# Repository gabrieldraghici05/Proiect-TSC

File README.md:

# Proiect-TSC

## Descriere generală

InkTime este un smartwatch construit în jurul microcontroller-ului nRF52840, utilizând un afișaj E-Paper. Proiectul este dezvoltat în Autodesk Fusion: de la concepția schemelor și rutarea unui PCB pe 4 straturi, până la integrarea mecanică finală în carcasă.

Principalele caracteristici:
- Procesare: nRF52840 (Cortex-M4F) cu conectivitate Bluetooth 5.0 integrată
- Afișaj: Ecran E-Paper (SPI)
- Senzori: Accelerometru BMA423 pentru pedometru și gesturi
- Baterie LiPo cu circuit de încărcare dedicat (BQ25180).
- Regulator DC/DC (RT6160) pentru o tensiune stabilă de 3.3V
- Fuel Gauge (MAX17048) pentru monitorizarea nivelului bateriei
- Driver haptic (DRV2605) pentru feedback
- Conectivitate USB-C pentru încărcare
- 3 butoane fizice pentru interacțiune

---

## Diagrama bloc

```text
                         +-------------------+
                         |    Baterie LiPo   |
                         +--------+----------+
                                  |
                         +--------v----------+
                         |  LiPo Charger     |  <-- USB-C (5V / VBUS)
                         |  BQ25180YBGR      |
                         +--------+----------+
                                  | VBAT (3.7-4.2V)
                         +--------v----------+
                         |  Fuel Gauge       |  <-- I2C --> nRF52840
                         |  MAX17048G+T10    |
                         +--------+----------+
                                  |
                         +--------v----------+
                         |  DC/DC Regulator  |  <-- I2C --> nRF52840
                         |  RT6160AWSC       |
                         +--------+----------+
                                  | 3V3
          +-----------------------+-----------------------+
          |                       |                       |
+---------v---------+   +---------v---------+   +---------v---------+
|   nRF52840 (U1)   |   |  ESD Protection   |   |   Butoane (x3)    |
|   Microcontroller |   |  USBLC6-2SC6Y     |   |   EVP-AKE31A      |
+---------+---------+   +-------------------+   +-------------------+
          |
    +-----+------+------+------+
    |            |      |      |
+---v---+  +----v--+  +-v---+ +-v---------+
| SPI   |  |  I2C  |  | SWD | | GPIO/ANT  |
+---+---+  +---+---+  +-----+ +-----------+
    |          |
+---v---+   +--+--+--+--+
|E-Paper|   | IMU | Haptic|
|Display|   |BMA423|DRV2605|
+-------+   +-------+-----+
```

---
## Bill of Materials (BOM)

| Cantitate | Componenta | Descriere | Referinta | 
|:---------:|:----------:|:---------:|:---------:|
| 1 | nRF52840 | Microcontroller ARM Cortex-M4, BT 5.0 | U1 | 
| 1 | BQ25180YBGR | LiPo Charger IC, 8-DSBGA | IC1 | 
| 1 | DRV2605YZFR | Haptic Driver ERM/LRA, 9-BGA | IC2 |
| 1 | BMA423 | IMU Accelerometru triaxial 12-bit | IC3 |
| 1 | MAX17048G+T10 | Fuel Gauge 1-Cell ModelGauge | U3 | 
| 1 | RT6160AWSC | Buck-Boost DC/DC Regulator I2C, 15-WL-CSP | IC9 | 
| 1 | USBLC6-2SC6Y | ESD Protection TVS Diode, SOT-23-6 | D3 | 
| 1 | KH-TYPE-C-16P | Conector USB-C 16 pini | J4 |
| 1 | 503480-2400 | Conector FPC/FFC 0.5mm 24 circuite | J1 | 
| 1 | DMG2305UX-7 | P-Channel MOSFET 20V/4.2A SOT-23 | Q2 | 
| 1 | SI1308EDL-T1-GE3 | N-Channel MOSFET 30V/1.5A SC-70 | Q3 | 
| 3 | MBR0530 | Dioda Schottky 30V/500mA SOD-123 | D1, D2, D5 | 
| 3 | EVP-AKE31A | Buton tactil SMD ultra-subtire | SW_DN, SW_ENT, SW_UP | 
| 1 | 2450AT18B100E | Antena 2.45GHz SMD | ANT1 | 
| 1 | FTC252012SR47MBCA | Inductor SMD 0.47uH 2016 | L7 | 
| 1 | 744043680 | Inductor SMD 68uH WE-TPC | L5 |
| 1 | TC2030-IDC | Conector Tag-Connect 6 pini SWD | J2 |
| 1 | X1 (32MHz) | Crystal 32MHz 2016 SMD | X1 |
| 1 | X2 (32.768kHz) | Crystal 32.768kHz 3215 SMD | X2 | 
| ~50 | Condensatoare SMD | 0201/0402, diverse valori (1pF - 22uF) | Cx | 
| ~15 | Rezistoare SMD | 0201, diverse valori (2.2Ω - 10kΩ) | Rx |
| ~4 | Inductoare SMD | 0402, diverse valori (3.9nH - 15nH, 10uH) | Lx |
| 14 | Test Pad TP20R | Test pad-uri SMD 2mm | TP_* |
| 1 | Solder Jumper SJ | Jumper SMD | SJ1 |

---

## Funcționalitate hardware

#### Componente și roluri
Sistemul este coordonat de nRF52840, care gestionează atât logica internă, stările de sleep pentru economisirea energiei, cât și comunicarea Bluetooth.

* Alimentare și Power Management: Bateria Li-Po este conectată direct la test pad-urile plăcii pentru a economisi spațiu pe verticală. Încărcarea este gestionată de BQ25180. Tensiunea bateriei este monitorizată precis de Fuel Gauge-ul MAX17048, iar alimentarea componentelor logice la 3.3V este asigurată de convertorul DC/DC RT6160 (ales în detrimentul unui LDO pentru un randament energetic superior).

* Interfața cu utilizatorul: Afișajul E-Paper este controlat prin SPI pentru o viteză mare de transfer, consumând energie doar la actualizarea imaginii. Input-ul se face prin 3 butoane tactile cu debouncing software, iar feedback-ul este asigurat de driverul haptic DRV2605 conectat la un actuator de tip shaker.

* Senzori: Accelerometrul BMA423 este legat pe magistrala I2C și este folosit pentru funcții precum ridicarea mâinii pentru aprindere (wake-on-wrist).

#### Interfețe de comunicație
* I2C: LiPo Charger, DC/DC, IMU, Fuel Gauge, Haptic Driver. (Folosește rezistențe de pull-up externe pentru stabilitate).

* SPI: E-Paper Display Connector (viteză mare de transmisie a datelor grafice).

---

## Pinii nRF52840

| Pin nRF52840 | Semnal | Modul conectat | Interfata | Descriere |
| :--------- | :--------- | :--------- | :--------- | :--------- |
| P0.02/AIN0 | SCK | E-Paper Display | SPI | Clock serial SPI |
| P0.03/AIN1 | MOSI | E-Paper Display | SPI | Date catre display (Master Out Slave In) |
| P0.05/AIN3 | CS | E-Paper Display | SPI | Chip Select display |
| P0.15 | EPD_RST | E-Paper Display | GPIO | Reset display |
| P0.16 | EPD_DC | E-Paper Display | GPIO | Data/Command select |
| P0.17 | EPD_BUSY | E-Paper Display | GPIO | Stare ocupata display |
| P0.06 | SCL | IMU, LiPo Charger, DC/DC, Fuel Gauge, Haptic | I2C | Clock linie I2C |
| P0.07 | SDA | IMU, LiPo Charger, DC/DC, Fuel Gauge, Haptic | I2C | Date linie I2C |
| P0.08 | IMU_INT2 | BMA423 | GPIO | Intrerupere 2 accelerometru |
| P1.08 | IMU_INT1 | BMA423 | GPIO | Intrerupere 1 accelerometru |
| P0.10/NFC2 | FUELGAUGE_ALT | MAX17048 | GPIO | Alarma nivel scazut baterie |
| P0.11 | CHARGER_PG | BQ25180 | GPIO | Semnal Power Good charger |
| P0.12 | HAPTIC_EN | DRV2605 | GPIO | Enable driver haptic |
| P0.13 | BTN_UP | SW_UP | GPIO | Buton sus |
| P0.14 | BTN_ENT | SW_ENT | GPIO | Buton enter/confirmare |
| P1.02 | BTN_DN | SW_DN | GPIO | Buton jos |
| D+ / D- | USB_DP / DM | USB-C / ESD | USB | Date USB diferentiale |
| VBUS | 5V USB | LiPo Charger | - | Alimentare 5V din USB |
| SWDIO / CLK | SWDIO / CLK| TC2030-IDC (J2) | SWD | Date programare/debug |
| SWO | SWO | TC2030-IDC (J2) | SWD | Trace output |
| P0.18/RESET | RESET | TC2030-IDC (J2) | GPIO | Reset hardware microcontroller |
| ANT | RF | 2450AT18B100E | RF | Antena Bluetooth 2.4GHz |
| XC1, XC2 | XTAL_32M | X1 (32 MHz) | Clock | Sursa de ceas principala |
| XL1, XL2 | XTAL_32K | X2 (32.768 kHz) | Clock | Sursa de ceas RTC (low power) |

---
## Design PCB si Modelare Mecanică 3D

### Stackup PCB — 4 straturi
Placa a fost realizată pe 4 straturi pentru a asigura o integritate a semnalului excelentă și o rutare compactă:

* Top (L1): Rutare semnal + componente SMD.

* L2: Plan de masă (GND solid) care oferă un return path scurt pentru toate semnalele.

* L3: Rutare secundară — acest strat a fost utilizat în principal pentru rezolvarea manuală a Airwire-urilor rămase în urma procesului de autorutare, asigurând finalizarea tuturor conexiunilor complexe.

* Bottom (L4): Rutare semnal secundar.

### Decizii de design notabile
* Decupaj Antenă (RF): Antena ceramică este poziționată pe marginea plăcii. Sub aceasta s-a realizat un decupaj complet al substratului pe toate planurile (ground clearance) pentru performanță radio optimă.

* Via-in-Pad: Pentru componentele BGA dense, a fost utilizată tehnologia via-in-pad pentru a salva spațiu, rutând semnalele direct din pad-uri.

* Pad-uri de Test: Au fost adăugate 14 test pad-uri pentru semnalele vitale (3V3, VBAT, SWD, I2C), pentru lipirea directă a bateriei.

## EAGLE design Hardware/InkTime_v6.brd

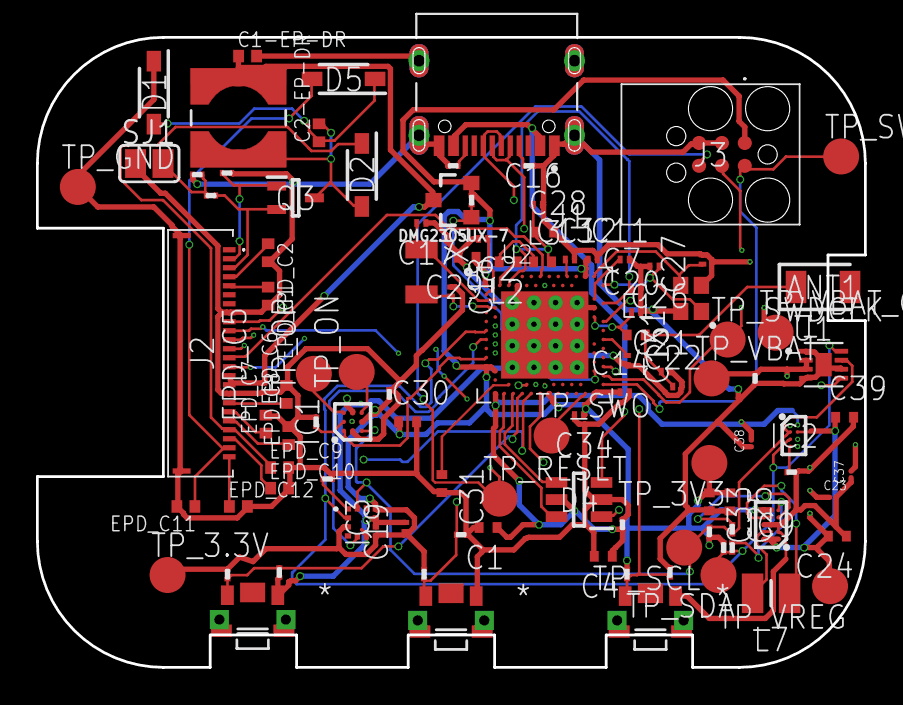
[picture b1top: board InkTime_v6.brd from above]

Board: 4 copper layers, 46.0 x 35.0 mm, 105 parts (0 on the bottom side), 70 nets.

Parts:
ANT1: 2450AT18B100E; 2450AT18B100E_ANTC3216X140N
C1, C29, C30, C31: 4.7μF; NORDIC_NRF_3_RESC0402_L
C1-EP-DR: 10uF; PERFECT_0402_0402
C2, C12, C14, C19, C34: 100nF; NORDIC_NRF_3_RESC0201_L
C2-EP-DR: 4.7uF/25V; PERFECT_0402_0402
C3, C5, C10, C32: 1uF; GRM011R60J152KE01L_1_0201
C4: 4.7uF; NORDIC_NRF_3_RESC0402_L
C6, C8, C9: 0.1uF; GRM011R60J152KE01L_1_0201
C7, C13, C22: N.C.; NORDIC_NRF_3_RESC0201_L
C11: 100pF; NORDIC_NRF_3_RESC0201_L
C15: 820pF; NORDIC_NRF_3_RESC0201_L
C16: 47nF; NORDIC_NRF_3_RESC0201_L
C17, C18, C26, C27: 12pF; NORDIC_NRF_3_RESC0201_L
C20, C21: 1pF; NORDIC_NRF_3_RESC0201_L
C23: 0.1uF; GRM011R60J152KE01L_2_CAPC0201X13N
C24, C39: 10uF; NORDIC_NRF_3_RESC0402_L
C25, C33: 22uF; NORDIC_NRF_3_RESC0402_L
C28: 1.0μF; NORDIC_NRF_3_RESC0402_L
C37, C38: 1uF; GRM011R60J152KE01L_2_CAPC0201X13N
D1, D2, D5: MBR0530; ESP32_C6_LIBRARY_5_SOD3716X135N
D4: USBLC6-2SC6Y; ESP32_C6_LIBRARY_3_SOT95P280X145-6N
DMG2305UX-7: 20V/4.2A/52mΩ/1.4W; ESP32_C6_LIBRARY_4_ESP32_C6_LIBRARY_4_ESP32_C6_LIBRARY_4_ES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
EPD_C1, EPD_C2, EPD_C6, EPD_C7, EPD_C8, EPD_C9, EPD_C10, EPD_C11, EPD_C12: 1uF/50V; PERFECT_0402_0402
EPD_C5: 0.1uF/50V; NORDIC_NRF_3_RESC0201_L
IC1: DRV2605YZFR; DRV2605YZFR_BGA9C50P3X3_144X144X62
IC2: BQ25180YBGR; BQ25180YBGR_BGA8C40P2X4_100X155X50
IC3: BMA421; BMA423_BMA423
IC9: RT6160AWSC; RT6160AWSC_BGA15C40P3X5_140X230X60
J1: KH-TYPE-C-16P; KH-TYPE-C-16P_KINGHELM_KH-TYPE-C-16P
J2: 503480-2400; 503480-2400_5034802400
J3: TC2030-IDC; TC2030-IDC_TC2030IDC
L1: 3.9nH; NORDIC_NRF_2_RESC0402_L
L2: 10μH; NORDIC_NRF_2_RESC0402_L
L3: 15nH; NORDIC_NRF_2_RESC0402_L
L5: 68uH; ESP32_C6_LIBRARY_2_IND_4828-WE-TPC_WRE
L7: FTC252012SR47MBCA; MLP2016SR47MT0S1_INDC2016X100N
Q3: SI1308EDL-T1-GE3; ESP32_C6_LIBRARY_6_SOT65P210X110-3N
R1, R2_EP_DR, R5, R7, R8: 10K; CPF0201D7K68C1_0201
R1_EP_DR1: 0.47; CPF0201D7K68C1_0201
R1_USB, R2_USB: 5K1; CPF0201D7K68C1_0201
R2, R3, R4: 0; CPF0201D7K68C1_0201
R17, R18: 3K3; ERA-1AEB3401C_0201
R_PWR_EPD: 10K; CPF0201D7K68C1_0201
R_TYPE_SEL: 2.2; CPF0201D7K68C1_0201
SJ1: ESP32_C6_LIBRARY_7_JUMPER_SJ
SW_DN: 2025-10-22_07-23-44_LIBRARY_EVP-AKE31ASW_EVP-AKE3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; 2025-10-22_07-23-44_LIBRARY_SW_EVP-AKE31A_PAN
SW_ENT: 2025-10-22_07-23-44_LIBRARY_EVP-AKE31ASW_EVP-AKE3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; 2025-10-22_07-23-44_LIBRARY_SW_EVP-AKE31A_PAN
SW_UP: 2025-10-22_07-23-44_LIBRARY_EVP-AKE31ASW_EVP-AKE3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; 2025-10-22_07-23-44_LIBRARY_SW_EVP-AKE31A_PAN
TP_3.3V, TP_3V3: HECTOR_WATCH_1_TPTP20R; HECTOR_WATCH_1_TP20R
TP_GND: HECTOR_WATCH_1_TPTP20R; HECTOR_WATCH_1_TP20R
TP_ON: HECTOR_WATCH_1_TPTP20R; HECTOR_WATCH_1_TP20R
TP_OP: HECTOR_WATCH_1_TPTP20R; HECTOR_WATCH_1_TP20R
TP_RESET: HECTOR_WATCH_1_TPTP20R; HECTOR_WATCH_1_TP20R
TP_SCL: HECTOR_WATCH_1_TPTP20R; HECTOR_WATCH_1_TP20R
TP_SDA: HECTOR_WATCH_1_TPTP20R; HECTOR_WATCH_1_TP20R
TP_SWDCLK: HECTOR_WATCH_1_TPTP20R; HECTOR_WATCH_1_TP20R
TP_SWIO: HECTOR_WATCH_1_TPTP20R; HECTOR_WATCH_1_TP20R
TP_SWO: HECTOR_WATCH_1_TPTP20R; HECTOR_WATCH_1_TP20R
TP_VBAT: HECTOR_WATCH_1_TPTP20R; HECTOR_WATCH_1_TP20R
TP_VBAT_GND: HECTOR_WATCH_1_TPTP20R; HECTOR_WATCH_1_TP20R
TP_VREG: HECTOR_WATCH_1_TPTP20R; HECTOR_WATCH_1_TP20R
U1: MAX17048G+T10; ESP32_C6_LIBRARY_SON50P200X200X80-9N
U2: NRF52840_QF; NORDIC_NRF_4_AQFN50P700X700X85_HS-74N
X1: 32MHz; NORDIC_NRF_BT-XTAL_2016_N
X2: 32.768kHz; NORDIC_NRF_1_XTAL_3215_N

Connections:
3V3: C8.2, C12.1, C14.1, C19.1, C25.1, C29.1, C30.1, C33.1, C34.1, DMG2305UX-7.2, IC1.C2, IC3.3, IC3.7, IC3.10, IC9.E2, IC9.E3, J3.1, R5.2, R7.2, R8.2, R17.1, R18.1, R_PWR_EPD.2, TP_3.3V.TP, TP_3V3.TP, U2.P$A22, U2.P$AD14, U2.P$AD23, U2.P$B1, U2.P$W1, U2.P$Y2
ALERT: U1.5, U2.P$J24
D+: D4.4, U2.P$AD6
D-: D4.6, U2.P$AD4
DEC1: C2.1, U2.P$C1
DEC3: C11.1, U2.P$D23
DEC4_6: C7.1, C16.1, C28.1, L3.2, U2.P$B5, U2.P$E24
DN: D4.1, J1.A7, J1.B7
DP: D4.3, J1.A6, J1.B6
EPD_3V3: C1-EP-DR.1, DMG2305UX-7.3, EPD_C5.2, J2.15, J2.16, L5.2
EPD_BUSY: J2.9, U2.P$AD12
EPD_CS: J2.12, U2.P$K2
EPD_DC: J2.11, U2.P$AD10
EPD_RST: J2.10, U2.P$AC11
GDR: J2.2, Q3.1, R2_EP_DR.2
GND: C1.2, C1-EP-DR.2, C2.2, C3.1, C4.2, C5.1, C6.2, C7.2, C8.1, C9.1, C10.1, C11.2, C12.2, C13.2, C14.2, C15.2, C16.2, C17.1, C18.1, C19.2, C20.2, C21.2, C22.2, C23.2, C24.1, C25.2, C26.2, C27.2, C28.2, C29.2, C30.2, C31.2, C32.1, C33.2, C34.2, C37.1, C38.1, C39.2, D1.1, D4.2, EPD_C1.2, EPD_C2.2, EPD_C5.1, EPD_C6.2, EPD_C7.2, EPD_C8.2, EPD_C9.2, EPD_C10.2, EPD_C11.2, EPD_C12.2, IC1.B1, IC1.B3, IC2.D2, IC3.8, IC3.9, IC9.B1, IC9.C1, IC9.C2, IC9.C3, J1.A1_B12, J1.A12_B1, J1.SH1, J1.SH2, J1.SH3, J1.SH4, J2.8, J2.17, J2.MP1, J2.MP2, J3.3, J3.5, R1.1, R1_USB.1, R2_EP_DR.1, R2_USB.2, R3.1, R_TYPE_SEL.1, SJ1.1, SW_DN.1, SW_ENT.1, SW_UP.1, TP_GND.TP, TP_VBAT_GND.TP, U1.1, U1.4, U1.6, U1.9, U2.P$74, U2.P$75, U2.P$76, U2.P$77, U2.P$78, U2.P$79, U2.P$80, U2.P$81, U2.P$82, U2.P$83, U2.P$84, U2.P$85, U2.P$86, U2.P$87, U2.P$88, U2.P$89, U2.P$90, U2.P$B7, U2.P$F23, X1.2, X1.4
HAPTIC_EN: IC1.A1, U2.P$U1
IMU_INT1: IC3.5, U2.P$N1
IMU_INT2: IC3.6, U2.P$P2
LX1: IC9.B2, IC9.B3, L7.1
LX2: IC9.D2, IC9.D3, L7.2
MOSI: J2.14, U2.P$B13
unnamed: C2-EP-DR.1, D1.2, D5.1
unnamed: C2-EP-DR.2, D2.2, L5.1, Q3.3
unnamed: R1_EP_DR1.1, R_TYPE_SEL.2, SJ1.2
unnamed: IC2.D1, R1.2
unnamed: C3.2, IC1.A2
unnamed: J1.B5, R2_USB.1
unnamed: EPD_C6.1, J2.18
unnamed: EPD_C7.1, J2.19
unnamed: EPD_C2.1, J2.4
unnamed: J1.A5, R1_USB.2
unnamed: EPD_C1.1, J2.5
unnamed: EPD_C8.1, J2.20
unnamed: EPD_C10.1, J2.22
unnamed: EPD_C12.1, J2.24
unnamed: IC9.D1, R4.2
unnamed: IC9.E1, R2.2
unnamed: IC3.1, R3.2
unnamed: C31.1, U2.P$AC5
unnamed: C17.2, U2.P$D2, X2.1
unnamed: C18.2, U2.P$F2, X2.2
unnamed: L2.1, U2.P$B3
unnamed: L2.2, L3.1
unnamed: C13.1, U2.P$A18
unnamed: C15.1, U2.P$N24
unnamed: C20.1, L1.1, U2.P$H23
unnamed: C26.1, U2.P$B24, X1.1
unnamed: C27.1, U2.P$A23, X1.3
OUT+: IC1.A3, TP_OP.TP
OUT-: IC1.C3, TP_ON.TP
P0.13: C5.2, R5.1, SW_UP.2, U2.P$AD8
P0.14: C10.2, R8.1, SW_ENT.2, U2.P$AC9
P1.01: DMG2305UX-7.1, R_PWR_EPD.1, U2.P$Y23
P1.02: C32.2, R7.1, SW_DN.2, U2.P$W24
PMIC_INT: IC2.A1, U2.P$T2
PREVGH: D2.1, EPD_C9.1, J2.21
PREVGL: D5.2, EPD_C11.1, J2.23
RESE: J2.3, Q3.2, R1_EP_DR1.2
RESET: J3.6, TP_RESET.TP, U2.P$AC13
RF: ANT1.1, C21.1, C22.1, L1.2
SCK: J2.13, U2.P$A12
SCL: IC1.C1, IC2.B1, IC3.12, R4.1, R17.2, TP_SCL.TP, U1.7, U2.P$M2
SDA: IC1.B2, IC2.C1, IC3.2, R2.1, R18.2, TP_SDA.TP, U1.8, U2.P$L1
SWDCLK: J3.4, TP_SWDCLK.TP, U2.P$AA24
SWDIO: J3.2, TP_SWIO.TP, U2.P$AC24
SWO: TP_SWO.TP, U2.P$AD22
VBAT: C9.2, C37.2, IC2.C2, TP_VBAT.TP, U1.2, U1.3
VBUS: C1.1, C4.1, C6.1, C38.2, D4.5, IC2.A2, J1.A4_B9, J1.A9_B4, U2.P$AD2
VREG: C23.1, C24.2, C39.1, IC2.B2, IC9.A1, IC9.A2, IC9.A3, TP_VREG.TP

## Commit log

2026-04-10 fisiere hardware
2026-04-10 fisiere manufacturing
2026-04-10 licenta si structura proiect
2026-04-10 structura proiect
2026-04-16 Review
2026-04-21 PDF Schematic
2026-04-21 gerbers final
2026-04-21 BOM si CPL actualizate
2026-04-21 PCB finalizat
2026-04-21 fisier Fusion360
2026-04-21 add Exploded View
2026-04-21 folder Images
2026-04-22 README

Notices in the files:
parts and their libraries:
COPYRIGHT: Copyright (C) 2024 Ultra Librarian. All rights reserved.
COPYRIGHT: Copyright (C) 2025 Ultra Librarian. All rights reserved.
